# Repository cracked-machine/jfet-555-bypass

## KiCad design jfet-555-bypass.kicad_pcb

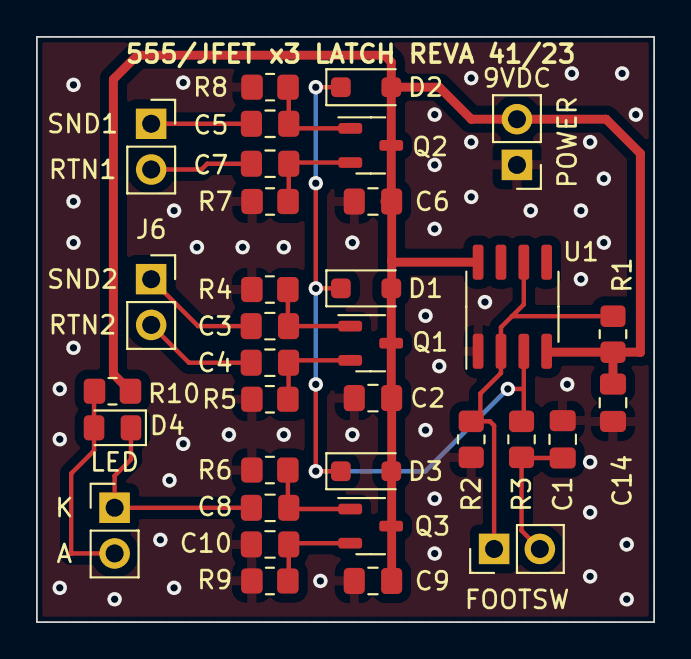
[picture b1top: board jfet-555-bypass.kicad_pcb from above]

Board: 2 copper layers, 34.3 x 32.5 mm, 34 parts (0 on the bottom side), 17 nets.

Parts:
C1, C2, C6, C9: 1uF; C_0805_2012Metric_Pad1.18x1.45mm_HandSolder
C3, C4, C5, C7, C8, C10: 4.7u; C_0805_2012Metric_Pad1.18x1.45mm_HandSolder
C14: 100nF; C_0805_2012Metric_Pad1.18x1.45mm_HandSolder
D1, D2, D3: D; D_SOD-123F
D4: LED; LED_0805_2012Metric_Pad1.15x1.40mm_HandSolder
J1: Footswitch_conn_01x02; PinHeader_1x02_P2.54mm_Vertical
J3: Power_Conn_01x02; PinHeader_1x02_P2.54mm_Vertical
J4: LED; PinHeader_1x02_P2.54mm_Vertical
J5: Signal1_Conn_01x02; PinSocket_1x02_P2.54mm_Vertical
J6: Signal2_Conn_01x02; PinSocket_1x02_P2.54mm_Vertical
Q1, Q2, Q3: MMBFJ177LT1G; SOT-23-3
R1, R2: 10K; R_0805_2012Metric_Pad1.20x1.40mm_HandSolder
R3: 100K; R_0805_2012Metric_Pad1.20x1.40mm_HandSolder
R4, R5, R6, R7, R8, R9: 330K; R_0805_2012Metric_Pad1.20x1.40mm_HandSolder
R10: 4K7; R_0805_2012Metric_Pad1.20x1.40mm_HandSolder
U1: NE555DR; SOIC-8_3.9x4.9mm_P1.27mm

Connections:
+9V: C2.1, C6.1, C9.1, C14.1, D1.2 (A), D2.2 (A), D3.2 (A), J3.2, Q1.3 (G), Q2.3 (G), Q3.3 (G), R1.2, R10.1, U1.4 (R), U1.8 (VCC)
/bypass/led_cathode_vdd: C8.1, D4.1 (K), J4.1
/clean_in_conn: C5.1, J5.1
/clean_out_conn: C7.2, J5.2
/fx_return_conn: C4.2, J6.2
/fx_send_conn: C3.1, J6.1
GND: C1.1, C2.2, C6.2, C9.2, C10.2, C14.2, J3.1, R2.1, R4.1, R5.1, R6.1, R7.1, R8.1, R9.1, U1.1 (GND)
unnamed: D1.1 (K), D2.1 (K), D3.1 (K), R3.2, U1.3 (Q)
unnamed: D4.2 (A), J4.2, R10.2
unnamed: J1.1, R1.1, R2.2, U1.2 (TR), U1.6 (THR)
unnamed: C1.2, J1.2, R3.1
unnamed: C3.2, Q1.1 (D), R4.2
unnamed: C4.1, Q1.2 (S), R5.2
unnamed: C5.2, Q2.1 (D), R8.2
unnamed: C7.1, Q2.2 (S), R7.2
unnamed: C8.2, Q3.1 (D), R6.2
unnamed: C10.1, Q3.2 (S), R9.2

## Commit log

2023-10-16 init commit
